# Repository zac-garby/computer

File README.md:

# Computer

These are the schematics for an 8-bit computer I'm designing, loosely based on [Ben Eater's YouTube series](https://www.youtube.com/playlist?list=PLowKtXNTBypGqImE405J2565dvjafglHU).

There's a pdf version of the schematics [here](schematic.pdf), although it might not always be up to date. Otherwise, you can open the project in [Kicad](http://kicad.org/).

I've also recreated the schematics in [Logisim](http://www.cburch.com/logisim/), to test that it all works properly before I build it in real life. You can download the Logisim file [here](simulation/computer.circ).

## Possible Future Improvements

 - In the decoder multiplexer, the input enable and output enable signals could be combined into the same signal. In reality, they will always be the same thing: it's pointless to output to the data bus unless something else is reading it, and vice versa. (This would involve changing `SUM_TO_ACC` to a multiplexed input signal.)

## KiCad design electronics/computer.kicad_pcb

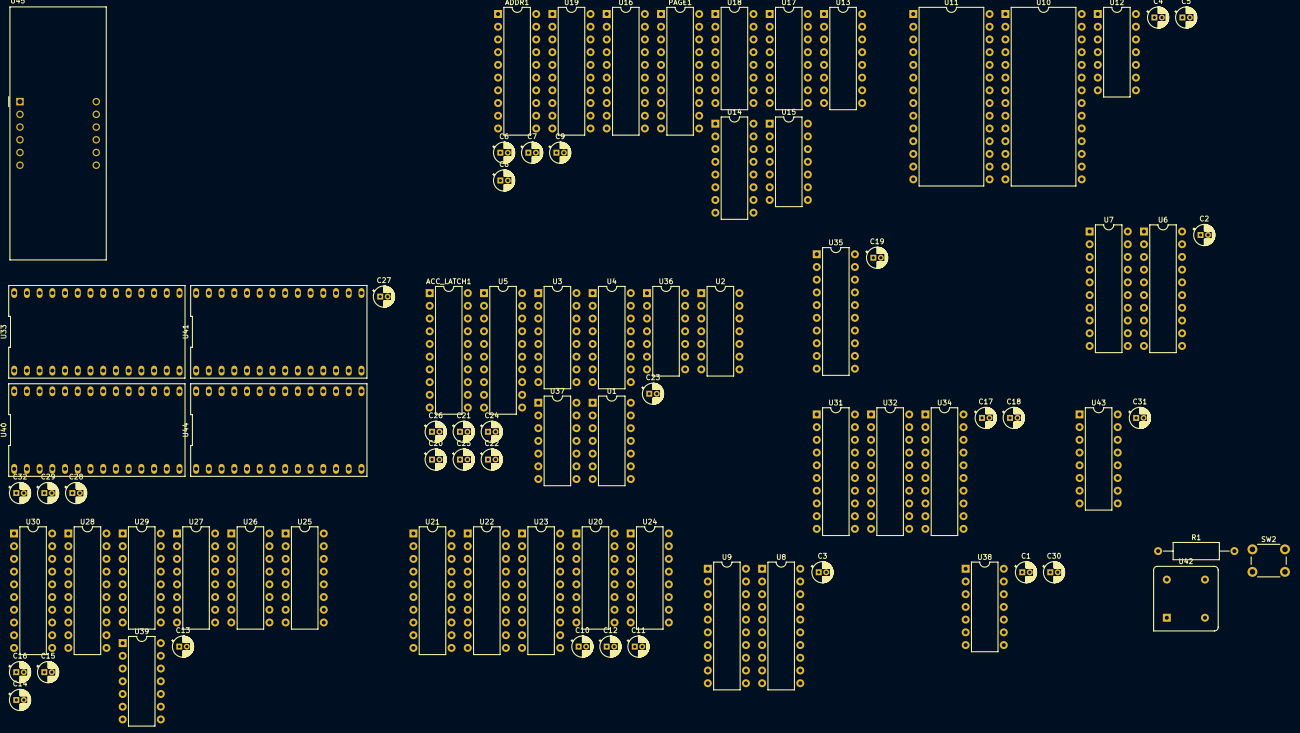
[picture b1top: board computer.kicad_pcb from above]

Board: 2 copper layers, 82 parts (0 on the bottom side), 204 nets, no tracks yet.

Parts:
ACC_LATCH1: 74LS377; DIP-20_W7.62mm
ADDR1: 74LS377; DIP-20_W7.62mm
C1, C2, C3, C4, C5, C6, C7, C8, C9, C10, C11, C12, C13, C14, C15, C16, C17, C18, C19, C20, C21, C22, C23, C24, C25, C26, C27, C28, C29, C30, C31, C32: 0.1µF; CP_Radial_D4.0mm_P1.50mm
PAGE1: 74LS377; DIP-20_W7.62mm
R1: 10k; R_Axial_DIN0309_L9.0mm_D3.2mm_P15.24mm_Horizontal
SW2: SW_Push; SW_PUSH_6mm
U1, U2, U39: 74LS386; DIP-14_W7.62mm
U3, U4: 74LS283; DIP-16_W7.62mm
U5, U7, U9, U16, U19, U22, U23, U28, U30, U34: 74LS245; DIP-20_W7.62mm
U6, U8, U21, U31, U32, U35: 74LS377; DIP-20_W7.62mm
U10, U11: AS6C62256-55PCN; DIP-28_W15.24mm
U12, U38: 74LS04; DIP-14_W7.62mm
U13, U14, U17, U18, U20, U24: 74LS157; DIP-16_W7.62mm
U15, U37: 74LS08; DIP-14_W7.62mm
U25, U26, U27, U29: 74LS163; DIP-16_W7.62mm
U33, U40, U41, U44: AT28C64B
U36: 74LS02; DIP-14_W7.62mm
U42: QX8T50B1.843200B50TT; Oscillator_DIP-8
U43: 74LS161; DIP-16_W7.62mm
U45: CC56-12CGKWA; CA56-12CGKWA

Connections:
+5V: ACC_LATCH1.20, ADDR1.20, C1.1, C2.1, C3.1, C4.1, C5.1, C6.1, C7.1, C8.1, C9.1, C10.1, C11.1, C12.1, C13.1, C14.1, C15.1, C16.1, C17.1, C18.1, C19.1, C20.1, C21.1, C22.1, C23.1, C24.1, C25.1, C26.1, C27.1, C28.1, C29.1, C30.1, C31.1, C32.1, PAGE1.20, SW2.2, U3.16, U4.16, U5.1, U5.20, U6.20, U7.1, U7.20, U8.20, U9.1, U9.20, U10.28, U11.28, U13.16, U14.16, U16.1, U16.20, U17.16, U18.16, U19.1, U19.20, U20.16, U21.20, U22.1, U22.20, U23.1, U23.20, U24.16, U25.1, U25.16, U26.1, U26.16, U27.1, U27.16, U28.1, U28.20, U29.1, U29.16, U30.1, U30.20, U31.20, U32.20, U33.27, U33.28, U34.1, U34.20, U35.20, U38.14, U40.27, U40.28, U41.27, U41.28, U42.1, U42.8, U43.7, U43.9, U43.10, U43.16, U44.27, U44.28
/A0: U10.10, U11.10, U13.3, U16.18, U25.3, U28.18
/A1: U10.9, U11.9, U13.6, U16.17, U25.4, U28.17
/A2: U10.8, U11.8, U13.10, U16.16, U25.5, U28.16
/A3: U10.7, U11.7, U13.13, U16.15, U25.6, U28.15
/A4: U10.6, U11.6, U14.3, U16.14, U26.3, U28.14
/A5: U10.5, U11.5, U14.6, U16.13, U26.4, U28.13
/A6: U10.4, U11.4, U14.10, U16.12, U26.5, U28.12
/A7: U10.3, U11.3, U14.13, U16.11, U26.6, U28.11
/A8: U10.25, U11.25, U17.3, U19.18, U27.3, U30.18
/A9: U10.24, U11.24, U17.6, U19.17, U27.4, U30.17
/A10: U10.21, U11.21, U17.10, U19.16, U27.5, U30.16
/A11: U10.23, U11.23, U17.13, U19.15, U27.6, U30.15
/A12: U10.2, U11.2, U18.3, U19.14, U29.3, U30.14
/A13: U10.26, U11.26, U18.6, U19.13, U29.4, U30.13
/A14: U10.1, U11.1, U18.10, U19.12, U29.5, U30.12
/A15: U10.20, U12.1, U18.13, U19.11, U29.6, U30.11
/ACC/~REG_EN: U15.6, U21.1
/Adder/ACC0: ACC_LATCH1.3, U5.18, U20.3, U22.18
/Adder/ACC1: ACC_LATCH1.4, U5.17, U20.6, U22.17
/Adder/ACC2: ACC_LATCH1.7, U5.16, U20.10, U22.16
/Adder/ACC3: ACC_LATCH1.8, U5.15, U20.13, U22.15
/Adder/ACC4: ACC_LATCH1.13, U5.14, U22.14, U24.3
/Adder/ACC5: ACC_LATCH1.14, U5.13, U22.13, U24.6
/Adder/ACC6: ACC_LATCH1.17, U5.12, U22.12, U24.10
/Adder/ACC7: ACC_LATCH1.18, U5.11, U22.11, U24.13
/Adder/C: U4.9, U35.4
/Adder/LATCH0: ACC_LATCH1.2, U3.5
/Adder/LATCH1: ACC_LATCH1.5, U3.3
/Adder/LATCH2: ACC_LATCH1.6, U3.14
/Adder/LATCH3: ACC_LATCH1.9, U3.12
/Adder/LATCH4: ACC_LATCH1.12, U4.5
/Adder/LATCH5: ACC_LATCH1.15, U4.3
/Adder/LATCH6: ACC_LATCH1.16, U4.14
/Adder/LATCH7: ACC_LATCH1.19, U4.12
/Adder/Z: U15.8, U35.3
/C: U33.7, U35.5, U40.7, U41.7, U44.7
/C0: U7.19, U33.11
/C1: U6.1, U33.12
/C2: U9.19, U33.13
/C3: U8.1, U33.15
/C4: U10.22, U11.22, U33.16
/C5: U10.27, U11.27, U33.17
/C6: U13.1, U14.1, U15.1, U33.18
/C7: U17.1, U18.1, U33.19
/C8: U16.19, U19.19, U40.11
/C9: U15.2, U40.12
/C10: U1.2, U1.6, U1.9, U1.13, U2.2, U2.6, U2.9, U2.13, U3.7, U40.13
/C11: U5.19, U15.4, U20.1, U24.1, U40.15
/C12: ACC_LATCH1.1, U22.19, U40.16
/C13: U35.1, U40.17
/C14: U23.19, U40.18
/C15: U15.5, U40.19
/C16: U25.9, U26.9, U27.9, U29.9, U41.11
/C17: U25.7, U25.10, U26.7, U26.10, U27.7, U27.10, U29.7, U29.10, U39.1, U41.12
/C18: U28.19, U30.19, U41.13
/C19: U15.13, U41.15
/C20: U31.1, U41.16
/C21: U34.19, U41.17
/C22: U32.1, U41.18
/CIR/OP0: U31.2, U33.5, U40.5, U41.5, U44.5
/CIR/OP1: U31.5, U33.4, U40.4, U41.4, U44.4
/CIR/OP2: U31.6, U33.3, U40.3, U41.3, U44.3
/CIR/OP3: U31.9, U33.25, U40.25, U41.25, U44.25
/CIR/OP4: U31.12, U33.24, U40.24, U41.24, U44.24
/CIR/OP5: U31.15, U33.21, U40.21, U41.21, U44.21
/CIR/OP6: U31.16, U33.23, U40.23, U41.23, U44.23
/CIR/OP7: U31.19, U33.2, U40.2, U41.2, U44.2
/D0: U1.1, U6.3, U7.18, U8.3, U9.18, U10.11, U11.11, U13.2, U17.2, U20.2, U23.18, U31.3, U32.3, U34.18
/D1: U1.5, U6.4, U7.17, U8.4, U9.17, U10.12, U11.12, U13.5, U17.5, U20.5, U23.17, U31.4, U32.4, U34.17
/D2: U1.8, U6.7, U7.16, U8.7, U9.16, U10.13, U11.13, U13.11, U17.11, U20.11, U23.16, U31.7, U32.7, U34.16
/D3: U1.12, U6.8, U7.15, U8.8, U9.15, U10.15, U11.15, U13.14, U17.14, U20.14, U23.15, U31.8, U32.8, U34.15
/D4: U2.1, U6.13, U7.14, U8.13, U9.14, U10.16, U11.16, U14.2, U18.2, U23.14, U24.2, U31.13, U32.13, U34.14
/D5: U2.5, U6.14, U7.13, U8.14, U9.13, U10.17, U11.17, U14.5, U18.5, U23.13, U24.5, U31.14, U32.14, U34.13
/D6: U2.8, U6.17, U7.12, U8.17, U9.12, U10.18, U11.18, U14.11, U18.11, U23.12, U24.11, U31.17, U32.17, U34.12
/D7: U2.12, U6.18, U7.11, U8.18, U9.11, U10.19, U11.19, U14.14, U18.14, U23.11, U24.14, U31.18, U32.18, U34.11
/MAR/~REG_ENB: ADDR1.1, PAGE1.1, U15.3
/ST0: U33.10, U40.10, U41.10, U43.14, U44.10
/ST1: U33.9, U40.9, U41.9, U43.13, U44.9
/ST2: U33.8, U40.8, U41.8, U43.12, U44.8
/Z: U33.6, U35.2, U40.6, U41.6, U44.6
CLK: U38.3, U43.2
GND: ACC_LATCH1.10, ADDR1.10, C1.2, C2.2, C3.2, C4.2, C5.2, C6.2, C7.2, C8.2, C9.2, C10.2, C11.2, C12.2, C13.2, C14.2, C15.2, C16.2, C17.2, C18.2, C19.2, C20.2, C21.2, C22.2, C23.2, C24.2, C25.2, C26.2, C27.2, C28.2, C29.2, C30.2, C31.2, C32.2, PAGE1.10, R1.2, U3.8, U4.8, U5.10, U6.10, U7.10, U8.10, U9.10, U10.14, U11.14, U13.8, U13.15, U14.8, U14.15, U16.10, U17.8, U17.15, U18.8, U18.15, U19.10, U20.8, U20.15, U21.10, U22.10, U23.10, U24.8, U24.15, U25.8, U26.8, U27.8, U28.10, U29.8, U30.10, U31.10, U32.10, U33.14, U33.20, U33.22, U34.10, U35.10, U38.7, U40.14, U40.20, U40.22, U41.14, U41.20, U41.22, U42.4, U43.8, U44.14, U44.20, U44.22
unnamed: ADDR1.2, U16.2
unnamed: ADDR1.3, U13.4
unnamed: ADDR1.4, U13.7
unnamed: ADDR1.5, U16.3
unnamed: ADDR1.6, U16.4
unnamed: ADDR1.7, U13.9
unnamed: ADDR1.8, U13.12
unnamed: ADDR1.9, U16.5
unnamed: ADDR1.12, U16.6
unnamed: ADDR1.13, U14.4
unnamed: ADDR1.14, U14.7
unnamed: ADDR1.15, U16.7
unnamed: ADDR1.16, U16.8
unnamed: ADDR1.17, U14.9
unnamed: ADDR1.18, U14.12
unnamed: ADDR1.19, U16.9
unnamed: PAGE1.2, U19.2
unnamed: PAGE1.3, U17.4
unnamed: PAGE1.4, U17.7
unnamed: PAGE1.5, U19.3
unnamed: PAGE1.6, U19.4
unnamed: PAGE1.7, U17.9
unnamed: PAGE1.8, U17.12
unnamed: PAGE1.9, U19.5
unnamed: PAGE1.12, U19.6
unnamed: PAGE1.13, U18.4
unnamed: PAGE1.14, U18.7
unnamed: PAGE1.15, U19.7
unnamed: PAGE1.16, U19.8
unnamed: PAGE1.17, U18.9
unnamed: PAGE1.18, U18.12
unnamed: PAGE1.19, U19.9
unnamed: R1.1, SW2.1
unnamed: U1.3, U3.6
unnamed: U1.4, U3.2
unnamed: U1.10, U3.15
unnamed: U1.11, U3.11
unnamed: U2.3, U4.6
unnamed: U2.4, U4.2
unnamed: U2.10, U4.15
unnamed: U2.11, U4.11
unnamed: U3.1, U5.3, U36.9
unnamed: U3.4, U5.2, U36.8
unnamed: U3.9, U4.7
unnamed: U3.10, U5.5, U36.12
unnamed: U3.13, U5.4, U36.11
unnamed: U6.2, U7.2
unnamed: U6.5, U7.3
unnamed: U6.6, U7.4
unnamed: U6.9, U7.5
unnamed: U6.12, U7.6
unnamed: U6.15, U7.7
unnamed: U6.16, U7.8
unnamed: U6.19, U7.9
unnamed: U8.2, U9.2
unnamed: U8.5, U9.3
unnamed: U8.6, U9.4
unnamed: U8.9, U9.5
unnamed: U8.12, U9.6
unnamed: U8.15, U9.7
unnamed: U8.16, U9.8
unnamed: U8.19, U9.9
unnamed: U11.20, U12.2
unnamed: U15.9, U37.3
unnamed: U15.10, U37.6
unnamed: U15.12, U42.5
unnamed: U20.4, U21.3
unnamed: U20.7, U21.4
unnamed: U20.9, U21.7
unnamed: U20.12, U21.8
unnamed: U21.2, U22.2, U23.2
unnamed: U21.5, U22.3, U23.3
unnamed: U21.6, U22.4, U23.4
unnamed: U21.9, U22.5, U23.5
unnamed: U21.12, U22.6, U23.6
unnamed: U21.13, U24.4
unnamed: U21.14, U24.7
unnamed: U21.15, U22.7, U23.7
unnamed: U21.16, U22.8, U23.8
unnamed: U21.17, U24.9
unnamed: U21.18, U24.12
unnamed: U21.19, U22.9, U23.9
unnamed: U25.2, U39.3
unnamed: U25.11, U28.5
unnamed: U25.12, U28.4
unnamed: U25.13, U28.3
unnamed: U25.14, U28.2
unnamed: U25.15, U26.2
unnamed: U26.11, U28.9
unnamed: U26.12, U28.8
unnamed: U26.13, U28.7
unnamed: U26.14, U28.6
unnamed: U26.15, U27.2
unnamed: U27.11, U30.5
unnamed: U27.12, U30.4
unnamed: U27.13, U30.3
unnamed: U27.14, U30.2
unnamed: U27.15, U29.2
unnamed: U29.11, U30.9
unnamed: U29.12, U30.8
unnamed: U29.13, U30.7
unnamed: U29.14, U30.6
unnamed: U32.2, U34.2
unnamed: U32.5, U34.3
unnamed: U32.6, U34.4
unnamed: U32.9, U34.5
unnamed: U32.12, U34.6
unnamed: U32.15, U34.7
unnamed: U32.16, U34.8
unnamed: U32.19, U34.9
unnamed: U36.1, U37.1
unnamed: U4.4, U5.6, U36.2
unnamed: U4.1, U5.7, U36.3
unnamed: U36.4, U37.2
unnamed: U4.13, U5.8, U36.5
unnamed: U4.10, U5.9, U36.6
unnamed: U36.10, U37.4
unnamed: U36.13, U37.5
unnamed: U38.5, U43.11
unnamed: U38.6, U43.1
~CLK: ACC_LATCH1.11, ADDR1.11, PAGE1.11, U6.11, U8.11, U21.11, U31.11, U32.11, U35.11, U38.4, U39.2

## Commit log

2019-08-12 Move electronics stuff into a subfolder
2019-08-12 Add a simulation
2019-08-12 Mention Logisim file
2019-08-12 Create a script to generate the decoder's ROM
2019-08-12 Add manual controler word override button
2019-08-12 Modify fetch stage
    Due to complications in the program counter and its interactions with other modules, I was forced to increment the program counter on its own in µ-code steps. This means only 4 steps are available to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
2019-08-12 Add an example program
    The format it's in is the one which can be read by RAM components in Logisim.
2019-08-12 Add a label for the output display
2019-08-12 Add a comment
2019-08-13 Add some more instructions
2019-08-13 Slight tweaking
2019-08-13 Add PAGE instruction
2019-08-13 Add pycache to .gitignore
2019-08-13 Make an assembler
2019-08-13 Write assembly code for each example
2019-08-13 Jumping instructions
2019-08-13 Add jumping instructions to assembler
2019-08-13 Make a new example program
    Counts from 1 to 10 then halts
2019-08-13 Tweaks
2019-08-14 Remove data and address debug injectors
2019-08-14 Enable simulation delay noise
2019-08-14 Move stuff around
2019-08-16 Add a reset button
2019-08-25 Add a stack pointer
    Will be used for calling and returning from functions
2019-08-25 Add the four new control signals
2019-08-25 Make RAM asynchronous
    Becuase in real life I will be using an asynchronous RAM chip
2019-08-25 Rearrange circuit a bit
2019-08-26 Implement the stack
    Also, a little bit of rearranging of the circuit diagram
2019-08-26 Add an example program using the stack
    Pushes two numbers and then pops them off in reverse order
2019-08-27 Make the opcode 7 bits and the µ-code step 4 bits
    This will allow 16 stages of microcode instead of the previous 8. As a result, more complicated instructions will be possible, but a mechanism to skip to the next instruction after a 0-control-word µ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
2019-08-27 Adapt decoder ROM for the new changes
2019-08-27 Replace decoder ROM with the new one
2019-08-27 Reset µ-code step if all control signals are 0
2019-08-29 Functions! CALL x and RETURN
2019-08-29 Add an example program using functions
2019-08-29 Add a screenshot
2019-08-29 Show the screenshot in the README
2019-08-30 Add docs
2019-09-02 Remove two unneeded control buffers from the ALU
2019-09-06 Some initial electronics design
    Not everything done yet, just committing to show progress and to get the changes out of the way.
2019-09-06 Rename C0-C29 signals to their actual names
2019-09-06 Modify hardware to multiplex data bus controls
    This greatly increases the number of available control signals without changing the eeprom word size (or in real life, without changing the number of eeproms).
    This works on the observation that at any given time, only one cpu component will be outputting to the data bus. The same goes for reading from the data bus.
2019-09-13 Rearrange decoder outputs
2019-09-13 Add a TODO list
2019-09-13 Make a new decoder rom generator program
    Since the multiplexing requires a new decoder
2019-09-13 Define a helper function: transfer
    Generates the bit pattern required to transfer data from one component to another
2019-09-25 Made some progress
    It seems now that the assembler doesn't work, so I'm committing now and then I can work on the assembler.
2019-10-04 A few changes
2021-01-13 typo!
2021-11-08 Update README.md
    https://forum.kicad.info/t/warning-avoid-all-links-to-kicad-pcb-org-use-kicad-org/31521
